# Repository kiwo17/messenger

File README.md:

# Messenger
The messenger is a display that shows daily quotes or phrases.

It works by using LED matrices, which allows to use tons of LED while using less pins. 

## About the Project

The messenger is going to be a multitasker!

I want it display daily encouraging motivating quotes or phrases to inspire in the morning. During the day
It the messenger is going to be displayed. It will have different states based on the weather. 

## The schematic

## The PCB

## 3D

### Difficulties

In the beginning I had A LOT of troubleshooting. 
I was very overwhelmed because I didn't quite understand the guide I was using.

- Firstly I didn't know which MCU I should chose, which made me change my schematic a couple of times
- Secondly and probably what consumed the most time and patience were the pins connections.
  I wasn't familiar with this so I had to research a lot.
- And lastly was the placement and the routing of the components. 

Thankfully I got help from very kind people and was able to complete this project. 

### Currently working on ...

- the Firmware
  
### Next steps ...

- finish code
- assemble

## BOM 

| Item | Qty | Supplier | Cost/item | Total Cost | link |
|---|---:|---|---:|---:|---|
| PCb | 1 | JLCPCB | $5.20 | $5.20 | [link](https://www.jlcpcb.com) |
| 100 nF Capacitor | 1 | Aliexpress | $1.17 | $1.17 | [link](https://de.aliexpress.com/item/1005011747293156.html) |
| 10 uF Capacitor | 1 | Aliexpress | $2.83 | $2.83 | [link](https://de.aliexpress.com/item/1005011747293156.html) |
| Raspberry Pi Pico | 1 | Aliexpress | $3.43 | $3.43 | [link](https://de.aliexpress.com/item/1005006839247100.html) |
| 5 pin socket | 1 | Aliexpress | $1.94 | $1.94 | [link](https://de.aliexpress.com/item/1005001418544370.html) |
| SN74AHCT125N | 1 | Aliexpress | $1.93 | $1.93 | [link](https://de.aliexpress.com/item/1005007655828920.html) |
| 5V, 2A USB power supply | 1 | Aliexpress | $2.40 | $2.40 | [link](https://de.aliexpress.com/item/1005013330943550.html) |
| Estimated total shipping | 1 |  |  | $13.44 |  |
### Total cost: $32.34

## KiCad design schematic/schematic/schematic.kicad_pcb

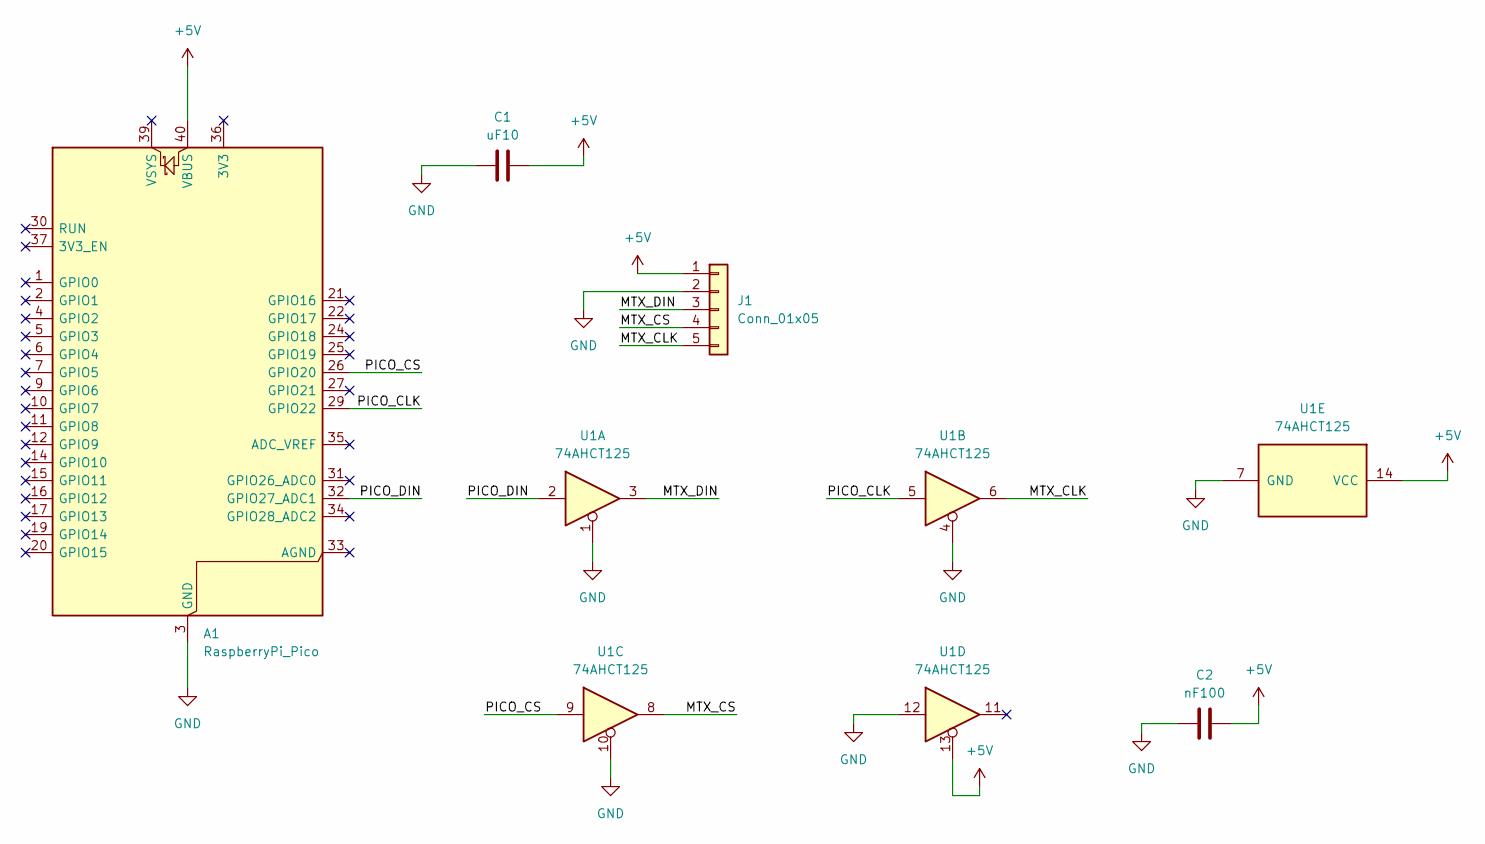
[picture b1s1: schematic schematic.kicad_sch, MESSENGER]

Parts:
A1: RaspberryPi_Pico; RaspberryPi_Pico_Common_Unspecified
C1: uF10; C_Disc_D5.1mm_W3.2mm_P5.00mm
C2: nF100; C_Disc_D5.1mm_W3.2mm_P5.00mm
J1: Conn_01x05; PinSocket_1x05_P2.54mm_Vertical
U1: 74AHCT125; DIP-14_W7.62mm

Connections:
+5V: A1.40 (VBUS), C1.1, C2.1, J1.1, U1.13, U1.14 (VCC)
/MTX_CLK: J1.5, U1.6
/MTX_CS: J1.4, U1.8
/MTX_DIN: J1.3, U1.3
/PICO_CLK: A1.29 (GPIO22), U1.5
/PICO_CS: A1.26 (GPIO20), U1.9
/PICO_DIN: A1.32 (GPIO27_ADC1), U1.2
GND: A1.3 (GND), A1.8 (GND), A1.13 (GND), A1.18 (GND), A1.23 (GND), A1.28 (GND), A1.38 (GND), C1.2, C2.2, J1.2, U1.1, U1.4, U1.7 (GND), U1.10, U1.12

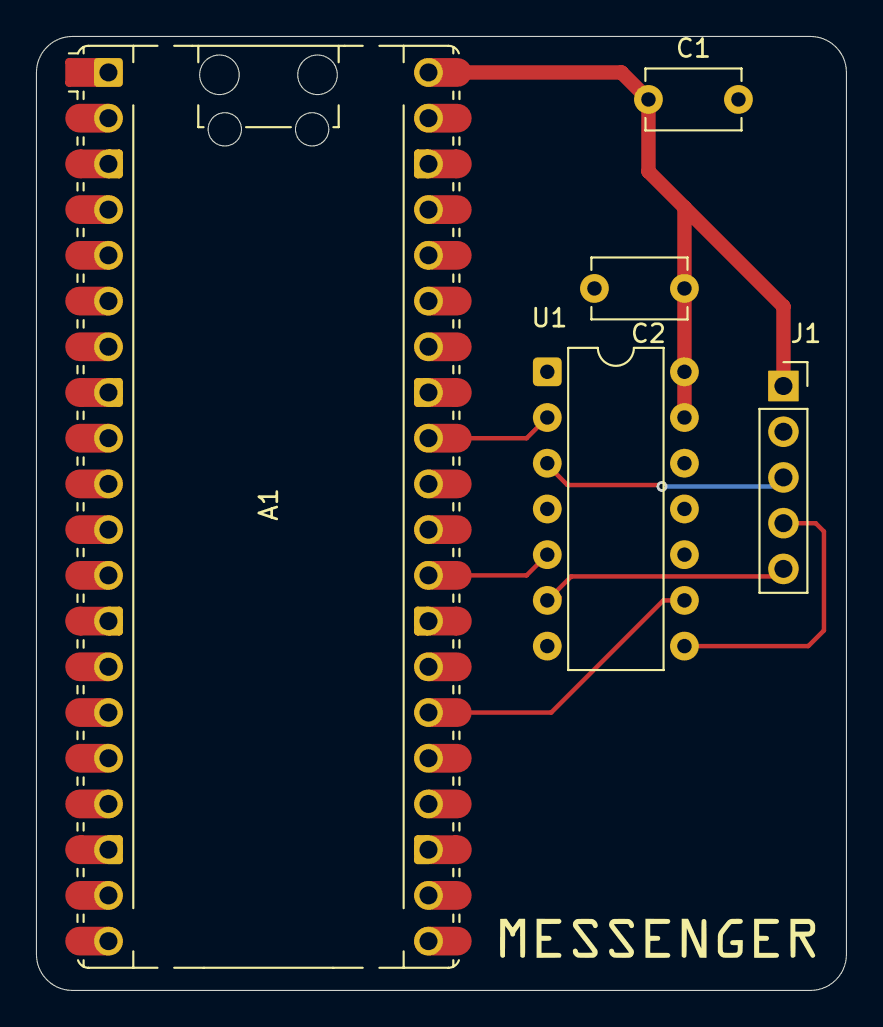
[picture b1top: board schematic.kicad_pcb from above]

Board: 2 copper layers, 45.0 x 53.0 mm, 5 parts (0 on the bottom side), 8 nets.

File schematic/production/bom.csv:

Designator,Footprint,Quantity,Value,LCSC Part #
A1,RaspberryPi_Pico_Common_Unspecified,1,RaspberryPi_Pico,
C1,C_Disc_D5.1mm_W3.2mm_P5.00mm,1,uF10,
C2,C_Disc_D5.1mm_W3.2mm_P5.00mm,1,nF100,
J1,PinSocket_1x05_P2.54mm_Vertical,1,Conn_01x05,
U1,DIP-14_W7.62mm,1,74AHCT125,
